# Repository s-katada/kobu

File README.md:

# kobu

自作分割キーボード「kobu」のモノレポです。世代ごとにディレクトリを分けています。

## ディレクトリ構成

| ディレクトリ | 中身 |
|---|---|
| [`v1/`](v1/) | 初代 kobu — KiCad PCB / ケース / ファームウェア (RMK・ZMK) / Web キーマップエディタ。詳細は [`v1/README.md`](v1/README.md) |
| [`v2/`](v2/) | kobu v2 — ケース / RMK ファームウェア。小指キーを左右 1 個ずつ追加した第 2 世代 (kobu2, PID 0x425A)。詳細は [`v2/README.md`](v2/README.md) |

## 開発環境

Nix flake / direnv。ルートの [`flake.nix`](flake.nix) が toolchain バージョンの単一情報源で、CI も同じ devshell で走ります。使い方は [`v1/README.md`](v1/README.md#開発環境) を参照。

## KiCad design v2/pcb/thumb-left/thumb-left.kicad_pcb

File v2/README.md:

# kobu v2

自作分割キーボード kobu の第 2 世代。v1 との**ハード面の違いは小指列最下段のキーを左右 1 個ずつ追加**したことだけです（19 → 20 キー/半分、計 40 キー）。

初代の PCB / ケース / ファームウェア / Web エディタは [`../v1/`](../v1/) にあります。

## ディレクトリ構成

| ディレクトリ | 中身 |
|---|---|
| [`case/`](case/) | ケースの STL |
| [`pcb/`](pcb/) | KiCad プロジェクト (`left-main` / `right-main` / `thumb-left` / `thumb-right`) |
| [`firmware/rmk/`](firmware/rmk/) | RMK ベースのファームウェア (Rust, thumbv7em-none-eabihf)。v1 の `firmware/rmk` からのフォーク。**クラシック構成（左手=セントラル）** |
| [`firmware/dongle/`](firmware/dongle/) | **Prospector ドングル構成**（ドングル=セントラル+ST7789 画面、左右両手=ペリフェラル）。keymap/behavior は `firmware/rmk/keyboard.toml` と要同期 |
| [`keymap-editor/`](keymap-editor/) | kobu2 専用の Web キーマップエディタ（実機の盤面をクリックして編集 + トラックボール調整）。どちらの構成でも無改修で動く（VID/PID・Via 0xC0 セマンティクス共通）|

## キーマップ

8 レイヤー構成です: **Mac**（デフォルト）/ **Win** / **Linux**（Mac ベース + Ctrl+H → Backspace のみ）/ **数字**（記号・矢印）/ **設定**（BLE プロファイル・F キー・メディア・レイヤー切替）/ **マウス**（トラックボール操作で自動起動）/ **Emacs** / **Neovim**。`▽` は下位レイヤーへの透過。最下行はマトリクス row 3 の実配置どおり「小指最下段キー + 親指クラスタ 4 キー」を 1 行に詰めて描いています。

盤面をまたぐ丸印は同時押し（コンボ）。コンボの出力は素のキーコードなので、Shift はホスト側で自然に効きます（`\` + Shift = `|`、`-` + Shift = `_` …）。

図の元データは [`firmware/rmk/keymap/kobu.yaml`](firmware/rmk/keymap/kobu.yaml) です。`keyboard.toml` とは**自動同期されない**ので、キーマップを変えたら yaml も手で直して描き直してください（devshell が stdout にバナーを出すため `<svg` 以降だけを取ります）:

```sh
cd firmware/rmk/keymap
nix develop ../../../..#firmware --command keymap draw kobu.yaml \
  | sed -n '/^<svg /,$p' > kobu.svg
```

## v1 とのファームウェア差分

- 追加キーは各半分の空いていたマトリクス交点 **ROW3×COL4**（小指列ネット × 親指行ネット）に配線。GPIO 追加なし・マトリクス寸法 (4×10) 変更なしで、keymap 座標では v1 で phantom だった **(3,0) / (3,9)** に載ります。レイヤー 0 の割り当ては左=Mission Control（Consumer 0x29F、Apple キーボードの F3 と同じ usage。2026-08-29 に LShift から変更）/ 右=RShift（他レイヤーは透過）。
  - 実基板で確認済み: 4 基板とも J1 は `1..4=/ROW0../ROW3`, `5..9=/COL0../COL4`, `10=NC` の**同一ピン配置**で、追加キーは各メイン基板の `SW16 = /ROW3 × /COL4`（小指列の最下段、既存最下行の 16mm 下）。/ROW3 が FFC pin4 でメインユニットへ届いています。
  - ⚠️ FFC ケーブルは v1 と逆で**ストレート結線（pin N ↔ pin N）**が必要です。v2 の FFC には電源線が無く（pin10 = NC、メイン基板はスイッチとダイオードのみの完全パッシブ）、誤ったケーブルでも MCU ピンが電源に張り付くことはありませんが、マトリクスは全く読めません。導通チェック手順は `firmware/rmk/keyboard.toml` 冒頭コメント参照。
- 識別子: name/product_name = **kobu2**、product_id = **0x425A**（VID `0x4b4f` と Vial keyboard UID は v1 と共通）。[web editor](../v1/web/rmk-editor/) は v1/v2 両方の PID を受け付けます。2 台目セットは `--features set-2` で **kobu2 squid / 0x425B**（後述）。
- それ以外（build.rs のレジストリパッチ、`src/`、メモリレイアウト、依存クレートのバージョン）は v1 と同一です。
  - うち 3 つは [`firmware/dongle/`](firmware/dongle/) のための 2026-08 追加: `patch_rmk_peripheral_manager_source_disambiguation`（**id≠0 のときだけ発火** → ペリフェラルが id0 の右手のみのクラシック構成では実行時に不活性）、`patch_rmk_split_connect_timeout_widen`（split 接続タイムアウト 5s→12s。クラシック構成では SCANNING_MUTEX が無競合でタイムアウト自体ほぼ発火しないため実質不可視）、`patch_rmk_split_adv_set_token`（広告のセット識別トークン。クラシック構成は `src/set_token.rs` で set 1=`0x41` / set 2=`0x42` を起動時に載せ、2 台同時通電でも左右が誤ペアしない。ドングルの `0x4B` とは別レンジ）。

## ⚠️ build.rs は v1 と同一内容に保つ

v1/v2 の build.rs はどちらも**共有 cargo registry のソースを in-place パッチ**します。両者が同一内容ならパッチは冪等で、どちらのツリーを先にビルドしても安全です。**片方だけにパッチを足して乖離させた場合**は、もう片方をビルドする前に

```sh
cargo clean --release -p rmk -p trouble-host -p rmk-macro
```

で 3 crate をパッチ済みソースから作り直してください（CI はジョブごとに pristine な registry なので無関係）。

## ビルド

v1 と同じで、リポジトリルートの devshell を使います:

```sh
cd v2/firmware/rmk        # direnv が firmware devshell を自動起動
cargo build --release --bin central
cargo build --release --bin peripheral
```

UF2 は CI が [firmware-latest リリース](../../releases/tag/firmware-latest)に `kobu2-rmk-central.uf2` / `kobu2-rmk-peripheral.uf2`（+ `-reset` 版）として公開します。ローカルで作る場合は devshell の `kobu-uf2conv`:

```sh
kobu-uf2conv target/thumbv7em-none-eabihf/release/central    kobu2-rmk-central.uf2
kobu-uf2conv target/thumbv7em-none-eabihf/release/peripheral kobu2-rmk-peripheral.uf2
```

### USB で central に焼く（キーマップ反映）

左手をデータ対応 USB で繋いだ状態で、firmware devshell から:

```sh
# clearlayout → 通常（保存キーマップを keyboard.toml で書き直し。BLE ボンドは残る）
v2/scripts/kobu-flash-central

# キーマップ以外の変更だけなら clearlayout なし
v2/scripts/kobu-flash-central --plain

# BLE のみのときに USB を挿すまで待ってから焼く
v2/scripts/kobu-flash-central --plain --wait
```

UF2 だけ渡す低レベル版は [`scripts/kobu-flash`](scripts/kobu-flash) です。

## 2 台の kobu2 を同時に使う（セット識別）

クラシック構成はデフォルトで **set 1**（split 広告トークン `0x41`、Mac 上の名前 `kobu2 octopus`、PID `0x425A`）です。2 台目は **同じ左右ペアごと**に `--features set-2` でビルドした UF2 を焼きます（トークン `0x42`、名前 `kobu2 squid`、PID `0x425B`）。トークンが違うと左右の初回ペアリングが相手セットに掴まれません。Mac 上も別名になるのでプロファイルを取り違えにくくなります。

```sh
# 2 台目セット（左右とも同じ feature）
cargo build --release --features set-2 --bin central
cargo build --release --features set-2 --bin peripheral
kobu-uf2conv target/thumbv7em-none-eabihf/release/central    kobu2-rmk-central-set2.uf2
kobu-uf2conv target/thumbv7em-none-eabihf/release/peripheral kobu2-rmk-peripheral-set2.uf2
```

**初回だけ** 各半分を `clear_storage=true` ビルド（または nuke）でボンドを消してから通常 UF2 を焼き、**1 セットずつ電源を入れて**左右を組み直してください。トークン付き広告は旧ファーム（token 0）とも相互に不可視なので、片側だけ古い UF2 のままだと繋がりません。

## XIAO の完全消去（flash nuke）

`kobu2-rmk-*-reset.uf2`（`clear_layout` ビルド）は保存済みキーマップを消すだけで、アプリ本体や BLE ボンドはそのまま残ります。XIAO を**本当にまっさら**（アプリなし・ブートローダのみ）に戻したいときは [`scripts/xiao-nuke.uf2`](scripts/xiao-nuke.uf2) を焼きます。RESET 2 連打 → ドラッグ & ドロップでも、[`scripts/kobu-flash`](scripts/kobu-flash) でも書き込めます:

```sh
# まっさらにするだけ
scripts/kobu-flash scripts/xiao-nuke.uf2

# まっさらにしてからクリーンインストール（nuke 後は自動でブートローダに
# 留まるので、そのまま続けて焼ける）
scripts/kobu-flash scripts/xiao-nuke.uf2 firmware/rmk/kobu2-rmk-central.uf2
```

- 消去範囲は **0x1000–0xC0000**: アプリ + RMK storage（0xA0000–0xC0000 のキーマップ・BLE ボンド・Vial 状態）で、ファームウェアが書き込む領域のすべて。MBR（0x0–0x1000）と Adafruit UF2 ブートローダ（0xF4000–）には触れません。終端を 0xC0000 で止めるのは、出荷版ブートローダ (0.6.1) の UF2 書き込みウィンドウが実測 0x1000–0xEA000 で、ウィンドウ外のブロックは受領カウントされず「全ブロック受領 → 自動リセット」が発火しなくなるため（0xF4000 終端で実害を確認済み。フラッシュ自体は書けるが物理 RESET が必要になる）。なお過去に ZMK を焼いた個体の settings（0xEA000 以降）は UF2 経由では消せないので、必要なら SWD で。
- 実行コードを含まない「全ブロック 0xFF のデータだけ」の UF2 で、ページ消去はブートローダの書き込みパスが行います。書き込み後は先頭ワードが 0xFFFFFFFF（= 有効なアプリなし）になるため、XIAO は再起動後も自動でブートローダ（XIAO-SENSE ドライブ）に留まり、そのまま次の UF2 を受け付けます。
- nRF52840 + Adafruit UF2 ブートローダの組み合わせなら v1 の XIAO にもそのまま使えます。
- キーボード側のボンドは消えますが、**ホスト側（macOS 等）の Bluetooth 設定に残った古いペアリングは別途削除**してください。

再生成は [`scripts/gen-xiao-nuke`](scripts/gen-xiao-nuke)（Python 3 標準ライブラリのみ、出力はバイト単位で再現可能）。CI も再生成してコミット済みファイルと一致することを検証します。

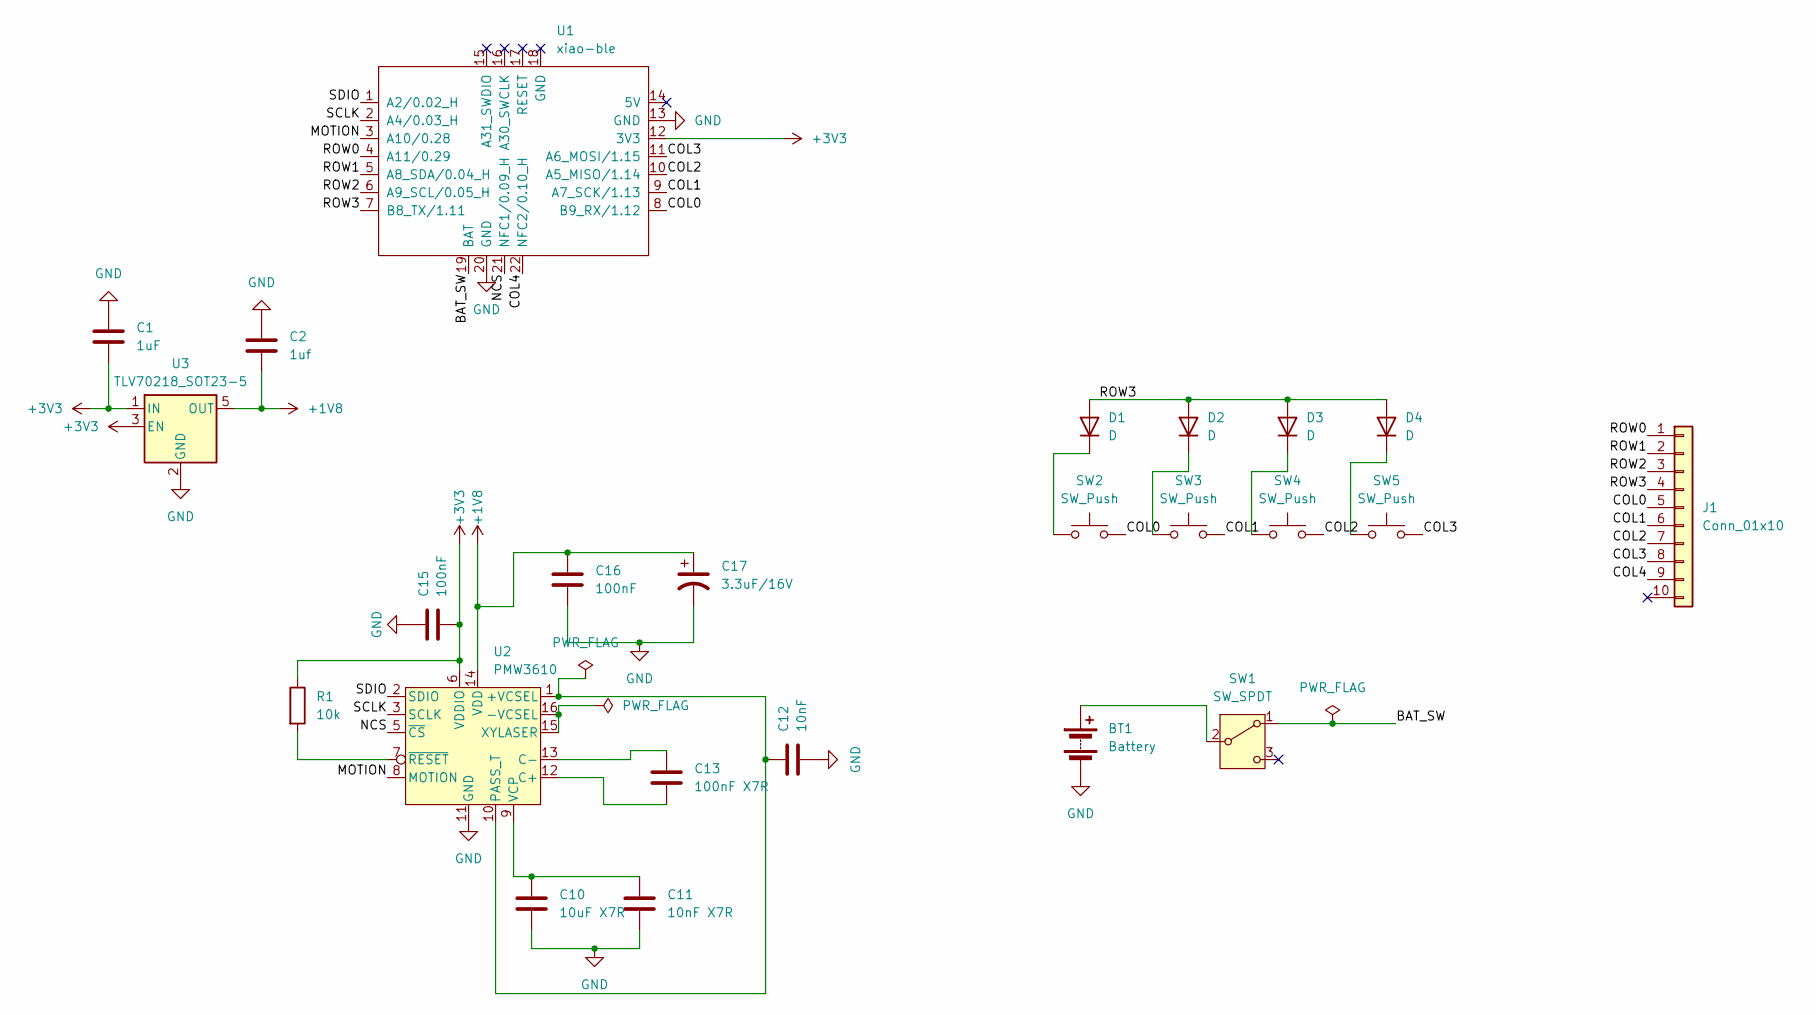
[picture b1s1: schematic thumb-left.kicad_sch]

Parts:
BT1: Battery; Molex_PicoBlade_53261-0271_1x02-1MP_P1.25mm_Horizontal
C1: 1uF; C_0402_1005Metric
C2: 1uf; C_0402_1005Metric
C10: 10uF X7R; C_0603_1608Metric
C11: 10nF X7R; C_0402_1005Metric
C12: 10nF; C_0402_1005Metric
C13: 100nF X7R; C_0402_1005Metric
C15, C16: 100nF; C_0402_1005Metric
C17: 3.3uF/16V; C_0603_1608Metric
D1, D2, D3, D4: D; D_SOD-123
J1: Conn_01x10; Hirose_FH12-10S-0.5SH_1x10-1MP_P0.50mm_Horizontal
R1: 10k; R_0603_1608Metric
SW1: SW_SPDT; TGSW_MSK-12D19
SW2, SW3, SW4, SW5: SW_Push; SW_Hotswap_Kailh_Choc_V2_1.00u
U1: xiao-ble; XIAO_nRF52840_wBAT_wNFC_1
U2: PMW3610
U3: TLV70218_SOT23-5; SOT-23-5

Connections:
+1V8: C2.2, C16.1, C17.1, U2.14 (VDD), U3.5 (OUT)
+3V3: C1.2, C15.2, R1.1, U1.12 (3V3), U2.6 (VDDIO), U3.1 (IN), U3.3 (EN)
/BAT_SW: SW1.1 (A), U1.19 (BAT)
/COL0: J1.5, SW2.2, U1.8 (B9_RX/1.12)
/COL1: J1.6, SW3.2, U1.9 (A7_SCK/1.13)
/COL2: J1.7, SW4.2, U1.10 (A5_MISO/1.14)
/COL3: J1.8, SW5.2, U1.11 (A6_MOSI/1.15)
/COL4: J1.9, U1.22 (NFC2/0.10_H)
/MOTION: U1.3 (A10/0.28), U2.8 (MOTION)
/NCS: U1.21 (NFC1/0.09_H), U2.5 (~CS)
/ROW0: J1.1, U1.4 (A11/0.29)
/ROW1: J1.2, U1.5 (A8_SDA/0.04_H)
/ROW2: J1.3, U1.6 (A9_SCL/0.05_H)
/ROW3: D1.2 (A), D2.2 (A), D3.2 (A), D4.2 (A), J1.4, U1.7 (B8_TX/1.11)
/SCLK: U1.2 (A4/0.03_H), U2.3 (SCLK)
/SDIO: U1.1 (A2/0.02_H), U2.2 (SDIO)
GND: BT1.2 (-), C1.1, C2.1, C10.1, C11.1, C12.2, C15.1, C16.2, C17.2, U1.13 (GND), U1.20 (GND), U2.11 (GND), U3.2 (GND)
unnamed: BT1.1 (+), SW1.2 (B)
unnamed: D1.1 (K), SW2.1
unnamed: D2.1 (K), SW3.1
unnamed: D3.1 (K), SW4.1
unnamed: D4.1 (K), SW5.1
unnamed: C12.1, U2.1 (+VCSEL), U2.10 (PASS_T)
unnamed: U2.15 (XYLASER), U2.16 (-VCSEL)
unnamed: C13.2, U2.12 (C+)
unnamed: C13.1, U2.13 (C-)
unnamed: C10.2, C11.2, U2.9 (VCP)
unnamed: R1.2, U2.7 (~RESET)

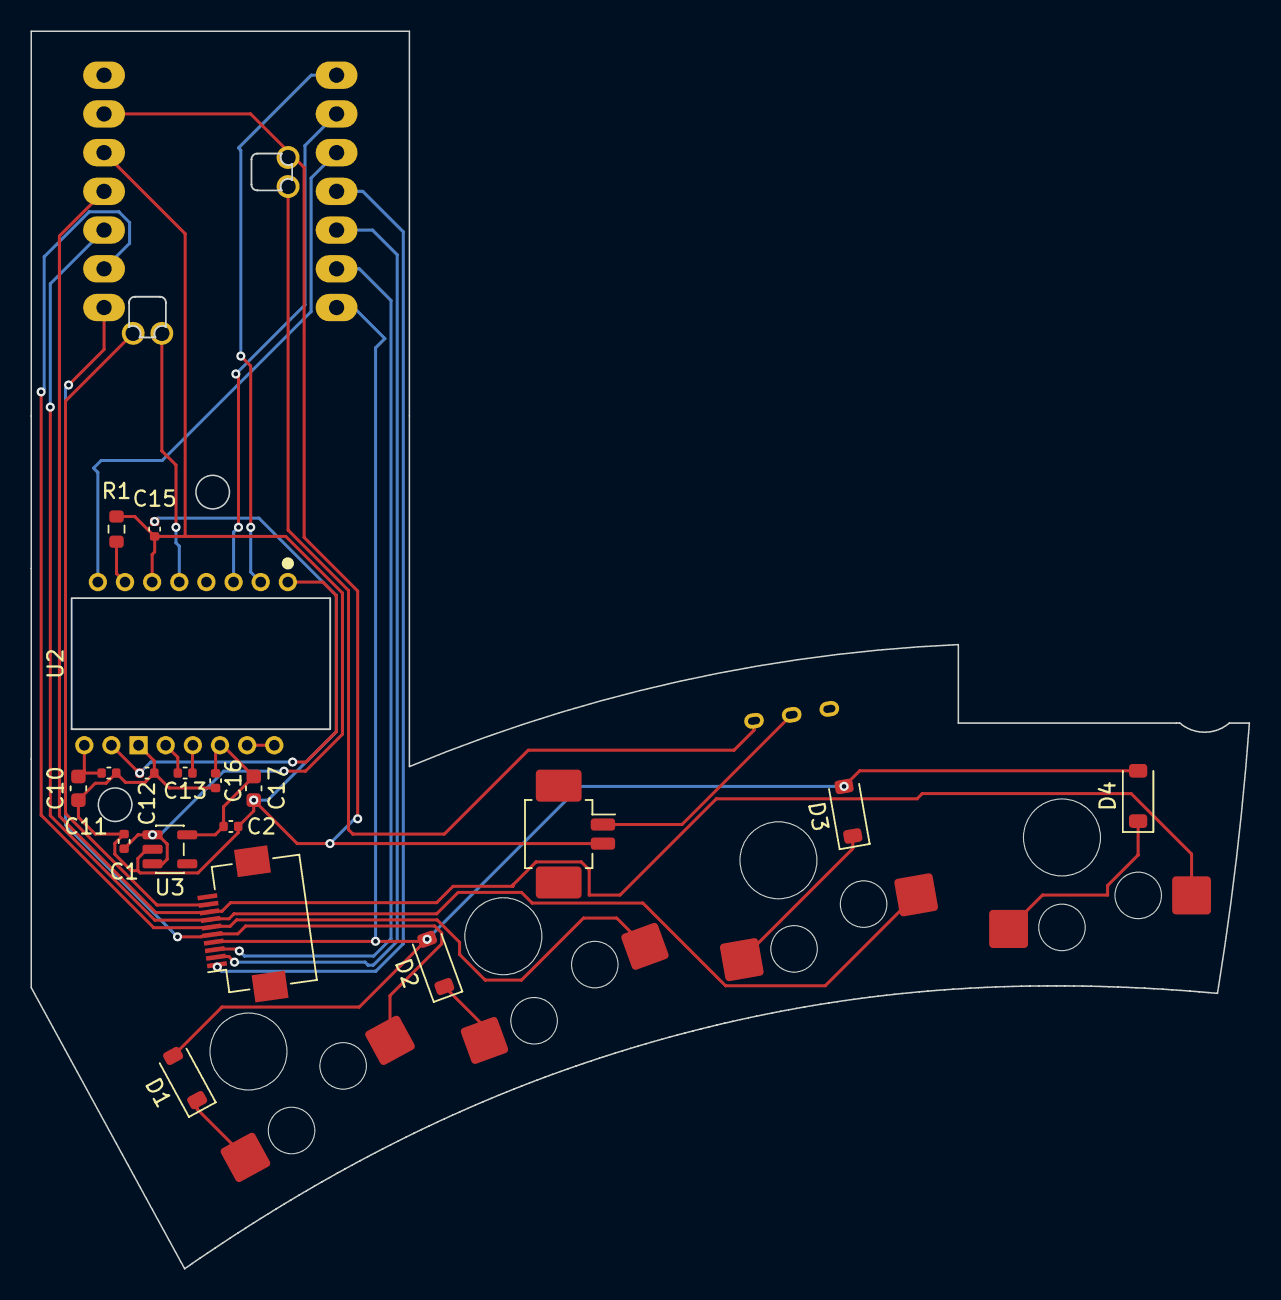
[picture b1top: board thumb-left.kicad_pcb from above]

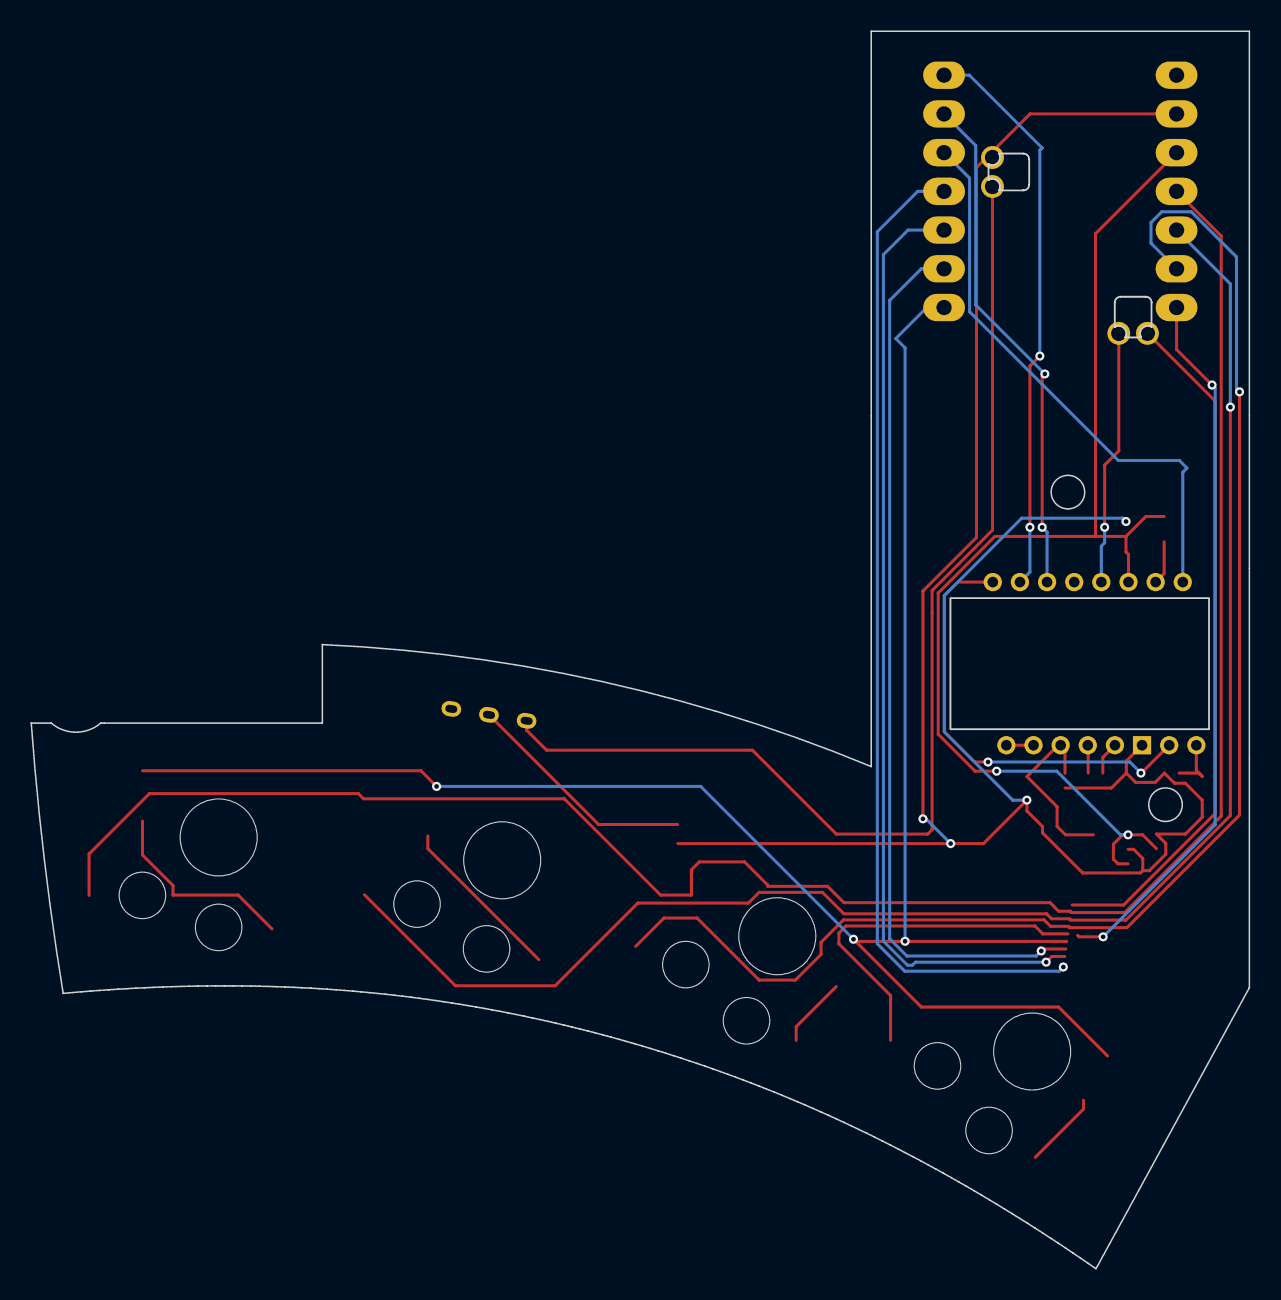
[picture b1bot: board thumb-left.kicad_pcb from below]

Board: 2 copper layers, 79.9 x 81.2 mm, 24 parts (5 on the bottom side), 28 nets.

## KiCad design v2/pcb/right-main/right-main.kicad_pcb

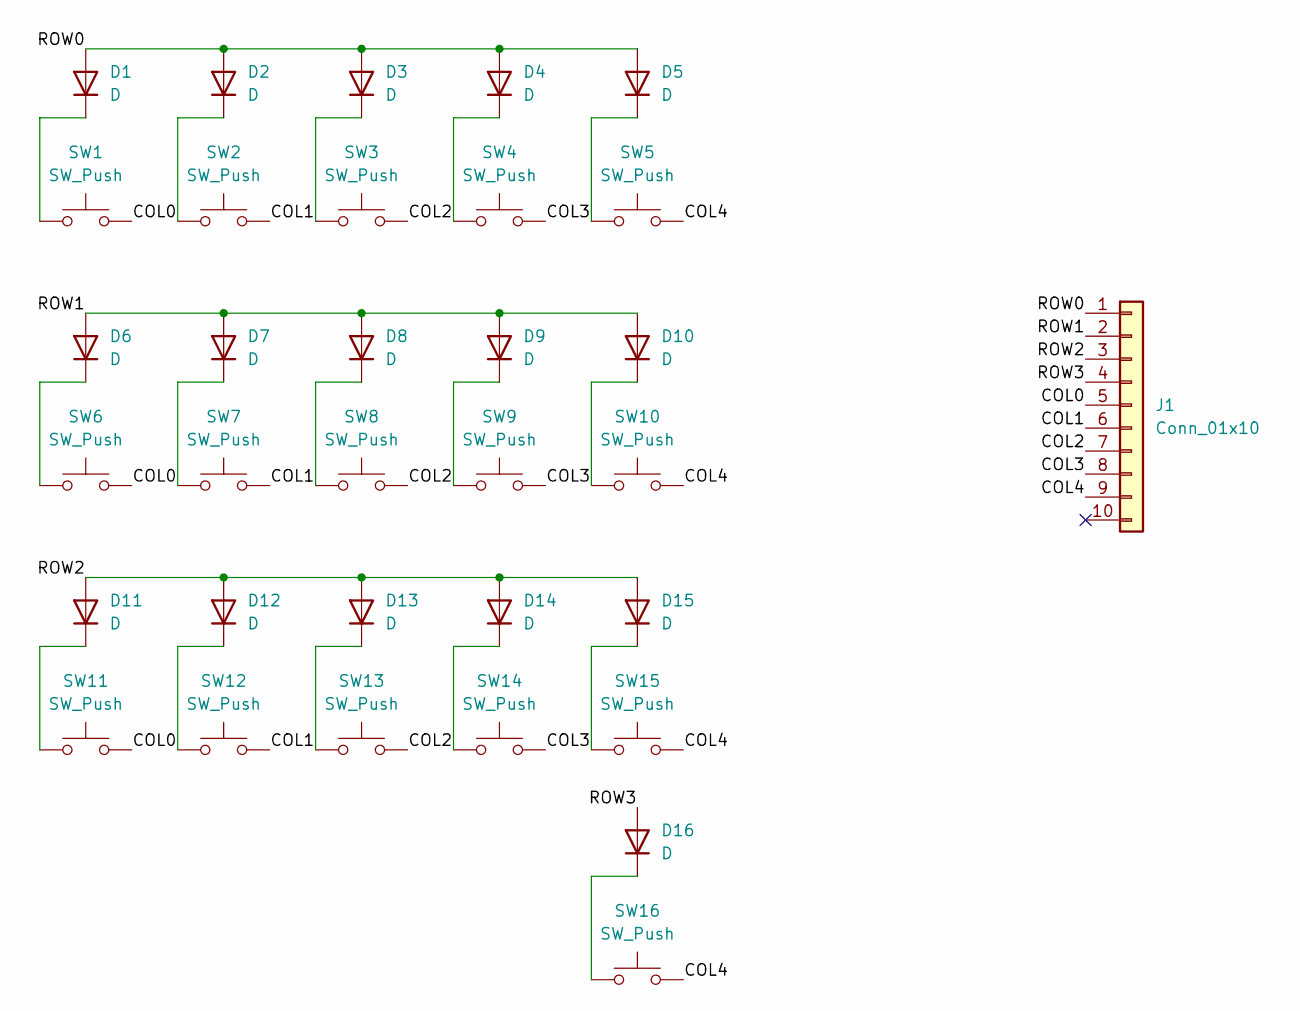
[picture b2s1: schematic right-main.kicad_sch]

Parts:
D1, D2, D3, D4, D5, D6, D7, D8, D9, D10, D11, D12, D13, D14, D15, D16: D; D_SOD-123
J1: Conn_01x10; Hirose_FH12-10S-0.5SH_1x10-1MP_P0.50mm_Horizontal
SW1, SW2, SW3, SW4, SW5, SW6, SW7, SW8, SW9, SW10, SW11, SW12, SW13, SW14, SW15, SW16: SW_Push; SW_Hotswap_Kailh_Choc_V2_1.00u

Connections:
/COL0: J1.5, SW1.2, SW6.2, SW11.2
/COL1: J1.6, SW2.2, SW7.2, SW12.2
/COL2: J1.7, SW3.2, SW8.2, SW13.2
/COL3: J1.8, SW4.2, SW9.2, SW14.2
/COL4: J1.9, SW5.2, SW10.2, SW15.2, SW16.2
/ROW0: D1.2 (A), D2.2 (A), D3.2 (A), D4.2 (A), D5.2 (A), J1.1
/ROW1: D6.2 (A), D7.2 (A), D8.2 (A), D9.2 (A), D10.2 (A), J1.2
/ROW2: D11.2 (A), D12.2 (A), D13.2 (A), D14.2 (A), D15.2 (A), J1.3
/ROW3: D16.2 (A), J1.4
unnamed: D1.1 (K), SW1.1
unnamed: D2.1 (K), SW2.1
unnamed: D3.1 (K), SW3.1
unnamed: D4.1 (K), SW4.1
unnamed: D5.1 (K), SW5.1
unnamed: D6.1 (K), SW6.1
unnamed: D7.1 (K), SW7.1
unnamed: D8.1 (K), SW8.1
unnamed: D9.1 (K), SW9.1
unnamed: D10.1 (K), SW10.1
unnamed: D11.1 (K), SW11.1
unnamed: D12.1 (K), SW12.1
unnamed: D13.1 (K), SW13.1
unnamed: D14.1 (K), SW14.1
unnamed: D15.1 (K), SW15.1
unnamed: D16.1 (K), SW16.1

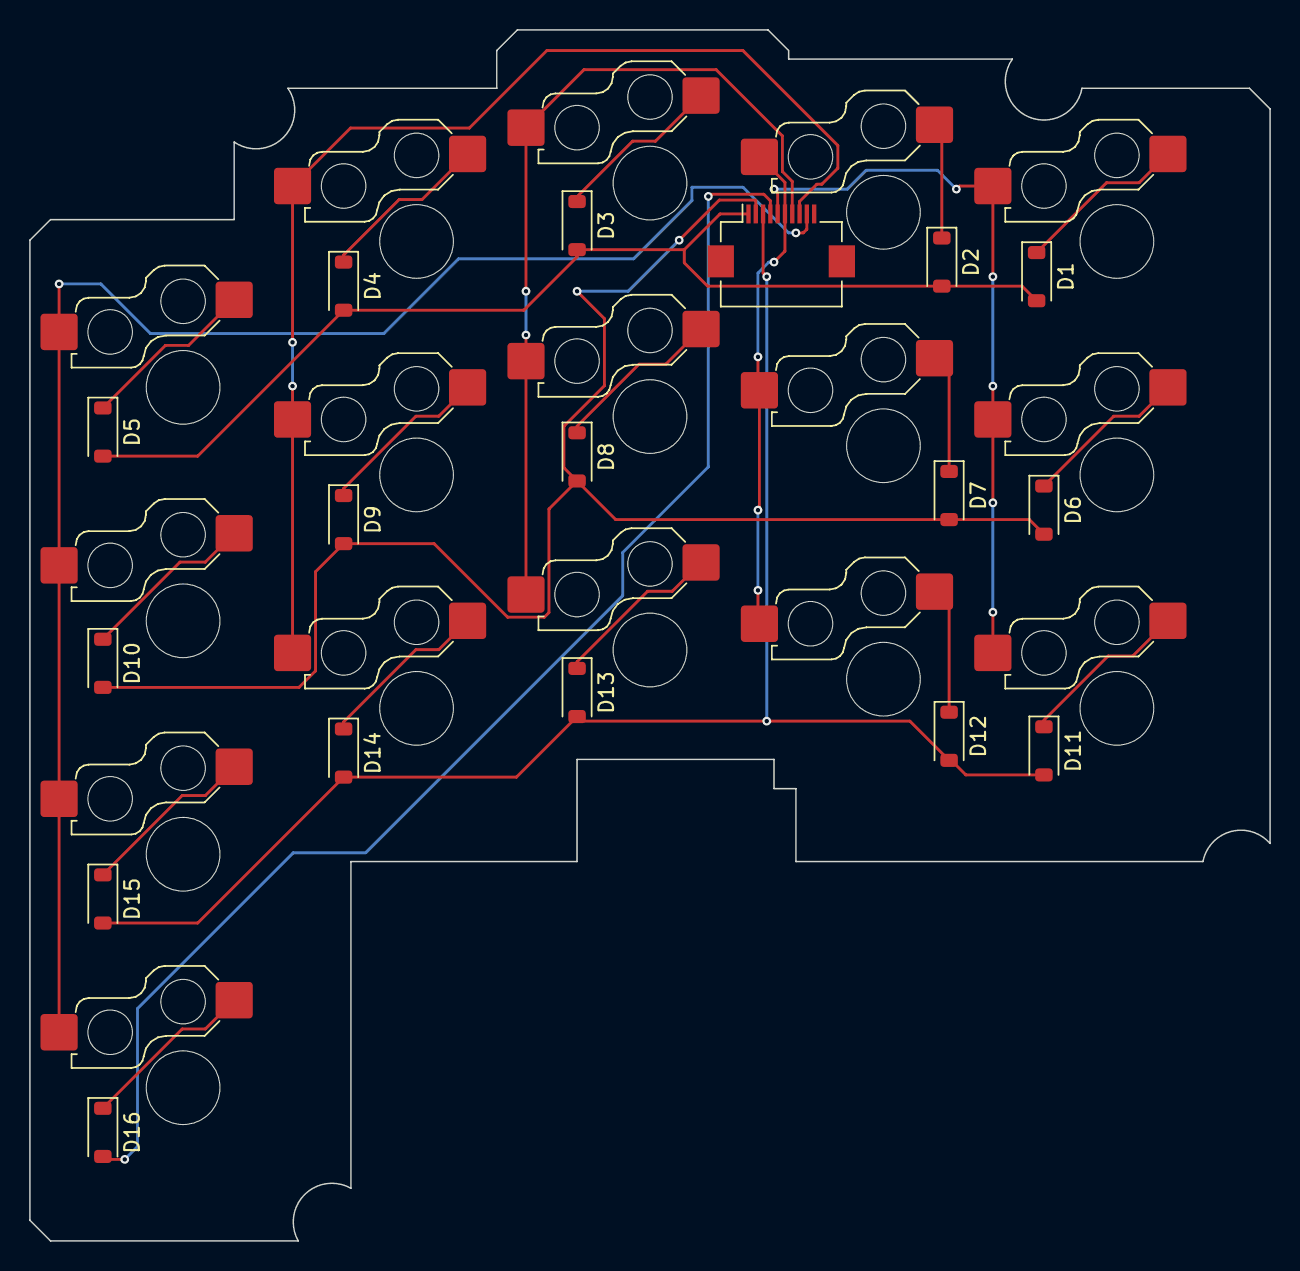
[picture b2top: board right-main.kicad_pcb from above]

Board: 2 copper layers, 85.0 x 83.0 mm, 33 parts (16 on the bottom side), 25 nets.

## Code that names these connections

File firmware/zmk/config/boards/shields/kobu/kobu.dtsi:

/*
 * kobu shield — shared hardware definition (both halves include this).
 *
 * kobu is a split keyboard with two Seeed XIAO nRF52840 BLE modules, a 4x5
 * scan matrix per half (unified into a 4x10 keymap), and one PMW3610 optical
 * trackball per half. LEFT = central (local ball drives SCROLL); RIGHT =
 * peripheral (ball forwarded over the split link, drives POINTER + auto-mouse).
 *
 * Pin map is taken verbatim from the RMK firmware's keyboard.toml (the
 * authoritative kobu spec). NOTE this differs from KobitoKey — kobu is a
 * different PCB:
 *   rows  (both halves, DRIVEN outputs): P0_29=D3, P0_04=D4, P0_05=D5, P1_11=D6
 *   cols  LEFT  (read inputs):  P0_10, P1_15, P1_14, P1_13, P1_12
 *   cols  RIGHT (read inputs):  P1_12, P1_13, P1_14, P1_15, P0_10  (see overlay)
 *   diodes anode-on-/ROW (per silkscreen) -> scan ROW->COL -> diode-direction
 *          = "row2col" (the OPPOSITE of KobitoKey's "col2row"); rows are the
 *          driven outputs, cols are the read inputs (pull-down).
 * P0_10 (NFC2) and P0_09 (NFC1) are NOT on the xiao_d nexus -> addressed as raw
 * &gpio0 10 / &gpio0 9 (requires CONFIG_NFCT_PINS_AS_GPIOS=y, set in the confs).
 */

#include <dt-bindings/zmk/matrix_transform.h>
#include <dt-bindings/zmk/input_transform.h>
#include <physical_layouts.dtsi>

/ {
    /* 4x5 matrix scan. Rows are shared L/R; cols default to the LEFT order and
     * are overridden in kobu_right.overlay. row2col => rows DRIVEN (active-high,
     * no pull), cols READ (active-high + pull-down). */
    kscan0: kscan0 {
        compatible = "zmk,kscan-gpio-matrix";
        diode-direction = "row2col";
        wakeup-source;

        row-gpios
            = <&xiao_d 3 GPIO_ACTIVE_HIGH>   /* P0_29  row0 */
            , <&xiao_d 4 GPIO_ACTIVE_HIGH>   /* P0_04  row1 */
            , <&xiao_d 5 GPIO_ACTIVE_HIGH>   /* P0_05  row2 */
            , <&xiao_d 6 GPIO_ACTIVE_HIGH>;  /* P1_11  row3 */

        /* LEFT col order [P0_10, P1_15, P1_14, P1_13, P1_12]. */
        col-gpios
            = <&gpio0 10 (GPIO_ACTIVE_HIGH | GPIO_PULL_DOWN)>   /* P0_10  col0 */
            , <&xiao_d 10 (GPIO_ACTIVE_HIGH | GPIO_PULL_DOWN)>  /* P1_15  col1 */
            , <&xiao_d  9 (GPIO_ACTIVE_HIGH | GPIO_PULL_DOWN)>  /* P1_14  col2 */
            , <&xiao_d  8 (GPIO_ACTIVE_HIGH | GPIO_PULL_DOWN)>  /* P1_13  col3 */
            , <&xiao_d  7 (GPIO_ACTIVE_HIGH | GPIO_PULL_DOWN)>; /* P1_12  col4 */
    };

    /* Unified 4 rows x 10 cols (left 0..4, right 5..9). Identity transform;
     * kobu_right.overlay adds col-offset = 5. */
    default_transform: keymap_transform0 {
        compatible = "zmk,matrix-transform";
        rows = <4>;
        columns = <10>;
        map = <
            RC(0,0) RC(0,1) RC(0,2) RC(0,3) RC(0,4)   RC(0,5) RC(0,6) RC(0,7) RC(0,8) RC(0,9)
            RC(1,0) RC(1,1) RC(1,2) RC(1,3) RC(1,4)   RC(1,5) RC(1,6) RC(1,7) RC(1,8) RC(1,9)
            RC(2,0) RC(2,1) RC(2,2) RC(2,3) RC(2,4)   RC(2,5) RC(2,6) RC(2,7) RC(2,8) RC(2,9)
            RC(3,0) RC(3,1) RC(3,2) RC(3,3) RC(3,4)   RC(3,5) RC(3,6) RC(3,7) RC(3,8) RC(3,9)
        >;
    };

    /* RIGHT (peripheral) trackball forwarded over the split link as input id 0.
     * The physical device + per-axis fix-ups are bound on the peripheral side
     * (kobu_right.overlay); the central consumes this split input via
     * tb_right_listener below. */
    split_inputs {
        #address-cells = <1>;
        #size-cells = <0>;

        tb_right_split: tb_right_split@0 {
            compatible = "zmk,input-split";
            reg = <0>;
        };
    };

    /* Listeners enabled per-half in the overlays. The LEFT ball (scroll) is a
     * central-local device; the RIGHT ball (pointer) arrives via the split. */
    tb_left_listener: tb_left_listener {
        compatible = "zmk,input-listener";
        status = "disabled";
    };

    tb_right_listener: tb_right_listener {
        compatible = "zmk,input-listener";
        status = "disabled";
        device = <&tb_right_split>;
    };

    /* Single physical layout (geometry + kscan + transform). */
    kobu_physical_layout: kobu_physical_layout {
        compatible = "zmk,physical-layout";
        display-name = "kobu";
        kscan = <&kscan0>;
        transform = <&default_transform>;

        keys =
            /* Row 0 */
              <&key_physical_attrs 100 100    0    0 0 0 0>
            , <&key_physical_attrs 100 100  100    0 0 0 0>
            , <&key_physical_attrs 100 100  200    0 0 0 0>
            , <&key_physical_attrs 100 100  300    0 0 0 0>
            , <&key_physical_attrs 100 100  400    0 0 0 0>
            , <&key_physical_attrs 100 100  650    0 0 0 0>
            , <&key_physical_attrs 100 100  750    0 0 0 0>
            , <&key_physical_attrs 100 100  850    0 0 0 0>
            , <&key_physical_attrs 100 100  950    0 0 0 0>
            , <&key_physical_attrs 100 100 1050    0 0 0 0>
            /* Row 1 */
            , <&key_physical_attrs 100 100    0  100 0 0 0>
            , <&key_physical_attrs 100 100  100  100 0 0 0>
            , <&key_physical_attrs 100 100  200  100 0 0 0>
            , <&key_physical_attrs 100 100  300  100 0 0 0>
            , <&key_physical_attrs 100 100  400  100 0 0 0>
            , <&key_physical_attrs 100 100  650  100 0 0 0>
            , <&key_physical_attrs 100 100  750  100 0 0 0>
            , <&key_physical_attrs 100 100  850  100 0 0 0>
            , <&key_physical_attrs 100 100  950  100 0 0 0>
            , <&key_physical_attrs 100 100 1050  100 0 0 0>
            /* Row 2 */
            , <&key_physical_attrs 100 100    0  200 0 0 0>
            , <&key_physical_attrs 100 100  100  200 0 0 0>
            , <&key_physical_attrs 100 100  200  200 0 0 0>
            , <&key_physical_attrs 100 100  300  200 0 0 0>
            , <&key_physical_attrs 100 100  400  200 0 0 0>
            , <&key_physical_attrs 100 100  650  200 0 0 0>
            , <&key_physical_attrs 100 100  750  200 0 0 0>
            , <&key_physical_attrs 100 100  850  200 0 0 0>
            , <&key_physical_attrs 100 100  950  200 0 0 0>
            , <&key_physical_attrs 100 100 1050  200 0 0 0>
            /* Row 3 (thumbs) */
            , <&key_physical_attrs 100 100    0  300 0 0 0>
            , <&key_physical_attrs 100 100  100  300 0 0 0>
            , <&key_physical_attrs 100 100  250  300 0 0 0>
            , <&key_physical_attrs 100 100  350  300 0 0 0>
            , <&key_physical_attrs 100 100  450  300 0 0 0>
            , <&key_physical_attrs 100 100  600  300 0 0 0>
            , <&key_physical_attrs 100 100  700  300 0 0 0>
            , <&key_physical_attrs 100 100  800  300 0 0 0>
            , <&key_physical_attrs 100 100  950  300 0 0 0>
            , <&key_physical_attrs 100 100 1050  300 0 0 0>
            ;
    };

    chosen {
        zmk,physical-layout = &kobu_physical_layout;
    };
};
/* RGB LED (led-red/green/blue) aliases + leds-enable are supplied by the
 * rgbled_adapter shield's boards/seeeduino_xiao_ble.overlay (pinned at the
 * zmk-rgbled-widget v0.3 tag in config/west.yml), so they are intentionally
 * NOT defined here. The XIAO onboard RGB LEDs are led0=P0_26 (R), led1=P0_30
 * (G), led2=P0_06 (B), common-anode. */

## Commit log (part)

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2026-05-10 feat: add top plate case
2026-05-12 feat: add case data
2026-05-15 fix(vial): drop phantom (3,0) and (3,9) cells from Vial layout
    The thumb row of the kobu matrix has phantom slots at (3,0) and (3,9)
    where /COL4 crosses /ROW3 — no switch is wired on the PCB, and
    keyboard.toml maps both positions to `No`. vial.json was still
    declaring them as drawable cells, which let users click them in
    vial.rocks and try to assign keycodes that can never fire.
    Replace the leading `{"x":2}, "3,0", ...` and trailing `..., "3,9"`
2026-05-15 feat(vial): pin host config and storage region for Vial use
    Add explicit [host] and [storage] blocks to keyboard.toml so the Vial
    runtime path is fully described in version control instead of relying
    on RMK defaults.
    [host] declares:
    * vial_enabled = true (explicit; matches RMK 0.8 default but guards
    against a future upstream default flip)
2026-05-15 feat(vial): wire user keycodes for 4-profile BLE management
    Two coupled changes so Vial labels and RMK actions agree.
    RMK 0.8's `process_user` derives the BLE action from
    `(User keycode index) - NUM_BLE_PROFILE`. kobu sets
    `ble_profiles_num = 4`, so the actual upstream mapping is:
    User0..User3 → switch to BLE profile 0..3
    User4 → next profile
2026-05-15 docs: document Vial keymap-editor workflow
    Add a "Vial でキーマップを編集する" section to README covering:
    * the USB-only constraint and which browsers work
    * connection steps via vial.rocks
    * the [[0,0],[0,9]] unlock chord — explained as matrix positions, not
    logical keycodes, since the distinction trips people up
    * layer 3's User0..User7 → BT0..BT3/Next/Prev/Clear/Switch table that
2026-05-15 docs: correct BLE Vial wording — firmware does support it, vial.rocks doesn't
    A precise version of the Vial-over-BLE story after re-reading rmk 0.8
    source and upstream issues.
    What was misleading in the previous draft:
    * The "BLE 接続中のみでは Vial を使えない" line implied RMK has no
    BLE Vial support, but rmk/src/ble/host_service/vial.rs ships a
    `BleVialServer` that exposes Vial over HID-over-GATT.
2026-05-15 ci: add Vial / keyboard.toml consistency lint
    A focused Python lint that runs on PRs touching vial.json,
    keyboard.toml, or the lint script itself, plus a GitHub Actions
    workflow to enforce it.
    The lint catches the five concrete failure modes the Vial-support
    issue series surfaced:
    1. matrix size mismatch between vial.json and keyboard.toml [layout]
2026-05-15 fix(vial): drop phantom (3,0) and (3,9) cells from Vial layout (#14)
    The thumb row of the kobu matrix has phantom slots at (3,0) and (3,9)
    where /COL4 crosses /ROW3 — no switch is wired on the PCB, and
    keyboard.toml maps both positions to `No`. vial.json was still
    declaring them as drawable cells, which let users click them in
    vial.rocks and try to assign keycodes that can never fire.
    Replace the leading `{"x":2}, "3,0", ...` and trailing `..., "3,9"`
2026-05-15 feat(vial): wire user keycodes for 4-profile BLE management (#16)
    Two coupled changes so Vial labels and RMK actions agree.
    RMK 0.8's `process_user` derives the BLE action from
    `(User keycode index) - NUM_BLE_PROFILE`. kobu sets
    `ble_profiles_num = 4`, so the actual upstream mapping is:
    User0..User3 → switch to BLE profile 0..3
    User4 → next profile
2026-05-15 feat(vial): pin host config and storage region for Vial use (#15)
    Add explicit [host] and [storage] blocks to keyboard.toml so the Vial
    runtime path is fully described in version control instead of relying
    on RMK defaults.
    [host] declares:
    * vial_enabled = true (explicit; matches RMK 0.8 default but guards
    against a future upstream default flip)
2026-05-15 ci: add Vial / keyboard.toml consistency lint (#18)
    A focused Python lint that runs on PRs touching vial.json,
    keyboard.toml, or the lint script itself, plus a GitHub Actions
    workflow to enforce it.
    The lint catches the five concrete failure modes the Vial-support
    issue series surfaced:
    1. matrix size mismatch between vial.json and keyboard.toml [layout]
2026-05-15 Squashed 'web/' content from commit 7dc58ec
    git-subtree-dir: web
    git-subtree-split: 7dc58ece8db228da6163cd86af7e335ebad0746b
2026-05-15 chore: merge kobu-config into web/ as a monorepo subdirectory
    Brings the kobu-config web app (previously a separate
    s-katada/kobu-config repository) into this monorepo under web/. The
    history is preserved as a squashed subtree merge so all the
    Phase 0-2 commits remain navigable from `git log -- web/`.
    Why move it:
    * kobu firmware and kobu-config web are tightly coupled — the Vial
2026-05-15 ci: split devshell into firmware / web / default for faster CI
    The original `devShells.default` had Rust + probe-rs + Node + pnpm in
    one shell. Running `nix develop` for the web CI was instantiating
    the full Rust toolchain (~14 minutes cold) just to run pnpm. Same
    story in reverse for the firmware CI if Node ever bumps.
    Split into three:
    default - firmware + web (kept as the local-dev catch-all)
2026-05-15 chore: merge kobu-config into web/ as a monorepo subdirectory (#42)
    * Squashed 'web/' content from commit 7dc58ec
    git-subtree-dir: web
    git-subtree-split: 7dc58ece8db228da6163cd86af7e335ebad0746b
    * chore: merge kobu-config into web/ as a monorepo subdirectory
    Brings the kobu-config web app (previously a separate
    s-katada/kobu-config repository) into this monorepo under web/. The
2026-05-15 chore: add per-directory .envrc files for nix-direnv
    The root already had `.envrc` with `use flake`, picking up
    `devShells.default` automatically on `cd kobu`. After the recent
    devshell split (default / firmware / web), the per-dir versions
    let direnv switch to the lighter shell when you change into a
    subdirectory:
    kobu/.envrc → use flake (full kit)
2026-05-15 chore: add per-directory .envrc files for nix-direnv (#43)
    The root already had `.envrc` with `use flake`, picking up
    `devShells.default` automatically on `cd kobu`. After the recent
    devshell split (default / firmware / web), the per-dir versions
    let direnv switch to the lighter shell when you change into a
    subdirectory:
    kobu/.envrc → use flake (full kit)
2026-05-15 chore: make subdirectory .envrc explicitly load the root flake
    Previously `firmware/.envrc` and `web/.envrc` used
    `use flake ..#<shell>`. That resolves to the root flake at evaluation
    time, but two things were slightly off:
    1. The bare `..` flakeref can be ambiguous to readers — it isn't
    obvious whether the parent directory has its own flake.nix or
    whether it walks further up. Tighten to `path:..#<shell>` so the
2026-05-15 chore: make subdirectory .envrc explicitly load the root flake (#44)
    Previously `firmware/.envrc` and `web/.envrc` used
    `use flake ..#<shell>`. That resolves to the root flake at evaluation
    time, but two things were slightly off:
    1. The bare `..` flakeref can be ambiguous to readers — it isn't
    obvious whether the parent directory has its own flake.nix or
    whether it walks further up. Tighten to `path:..#<shell>` so the
2026-05-15 chore: bump Node to 26.1.0 via flake.nix
    nodejs_26 hasn't landed in nixos-unstable yet (2026-05-16). It is
    available on the staging-next branch, so add a second nixpkgs input
    pointing there and route only `nodejs_26` through it — everything
    else (Rust, probe-rs, flip-link, etc.) stays on the stable
    nixos-unstable channel.
    flake.nix:
2026-05-16 ci: invalidate cargo cache when flake.lock changes
    After bumping `flake.lock` for nodejs_26 the fenix lock advanced too,
    which silently moves the Rust toolchain to a new /nix/store path.
    Swatinem/rust-cache restored the previous \`target/\` directory whose
    build-script binaries pointed at the old store path, and the firmware
    build then failed with:
    error: failed to run custom build command for `bindgen v0.72.1`
2026-05-23 chore(ci): gate web deploy on Cloudflare secrets so missing creds don't fail the workflow
    Every push to main has been failing the Web workflow because the
    deploy job runs `wrangler deploy` with empty `CLOUDFLARE_API_TOKEN`
    / `CLOUDFLARE_ACCOUNT_ID`, exits 1 with an explicit error message,
    and the whole run is reported as a failure.
    Add a `check-deploy-secrets` gate job between `ci` and `deploy`.
    It reads the secrets into env, exports a `cloudflare_configured`
2026-05-23 chore(ci): gate web deploy on Cloudflare secrets so missing creds don't fail the workflow (#57)
    Every push to main has been failing the Web workflow because the
    deploy job runs `wrangler deploy` with empty `CLOUDFLARE_API_TOKEN`
    / `CLOUDFLARE_ACCOUNT_ID`, exits 1 with an explicit error message,
    and the whole run is reported as a failure.
    Add a `check-deploy-secrets` gate job between `ci` and `deploy`.
    It reads the secrets into env, exports a `cloudflare_configured`
2026-05-23 fix(ci): override working-directory in check-deploy-secrets gate
    The Web workflow declares `defaults: run: working-directory: web` at
    the workflow level, which applies to every job. The
    check-deploy-secrets gate added in #57 doesn't run actions/checkout
    — it's a cheap secret probe with no source files to consult — so
    the runner's `web/` directory doesn't exist when bash tries to cd
    into it. Result: 'No such file or directory' before any command
2026-05-24 Add Cloudflare Workers configuration
2026-05-27 chore: ケースデータを整理
2026-06-01 chore: caseデータの配置を調整
2026-06-08 Revert "tune(firmware/zmk): hold-tap tapping-term 200 -> 170ms"
    This reverts commit 68535cdd89731c7e5b8195503aede5961ef687ec.
2026-06-11 feat: change author
2026-06-11 Revert "tune(firmware/rmk): TRUE KobitoKey hold-tap parity — per-key flavors instead of uniform tap-preferred"
    This reverts commit 3e5a86254db59f20163eff63c48085591c38f5f7.
2026-06-11 Revert "fix(firmware/rmk): route morse taps & combo outputs through the fork table (choke-point patch)"
    This reverts commit 4303eedb8236f65ebc0fb5110b15aeb1a604fab5.
